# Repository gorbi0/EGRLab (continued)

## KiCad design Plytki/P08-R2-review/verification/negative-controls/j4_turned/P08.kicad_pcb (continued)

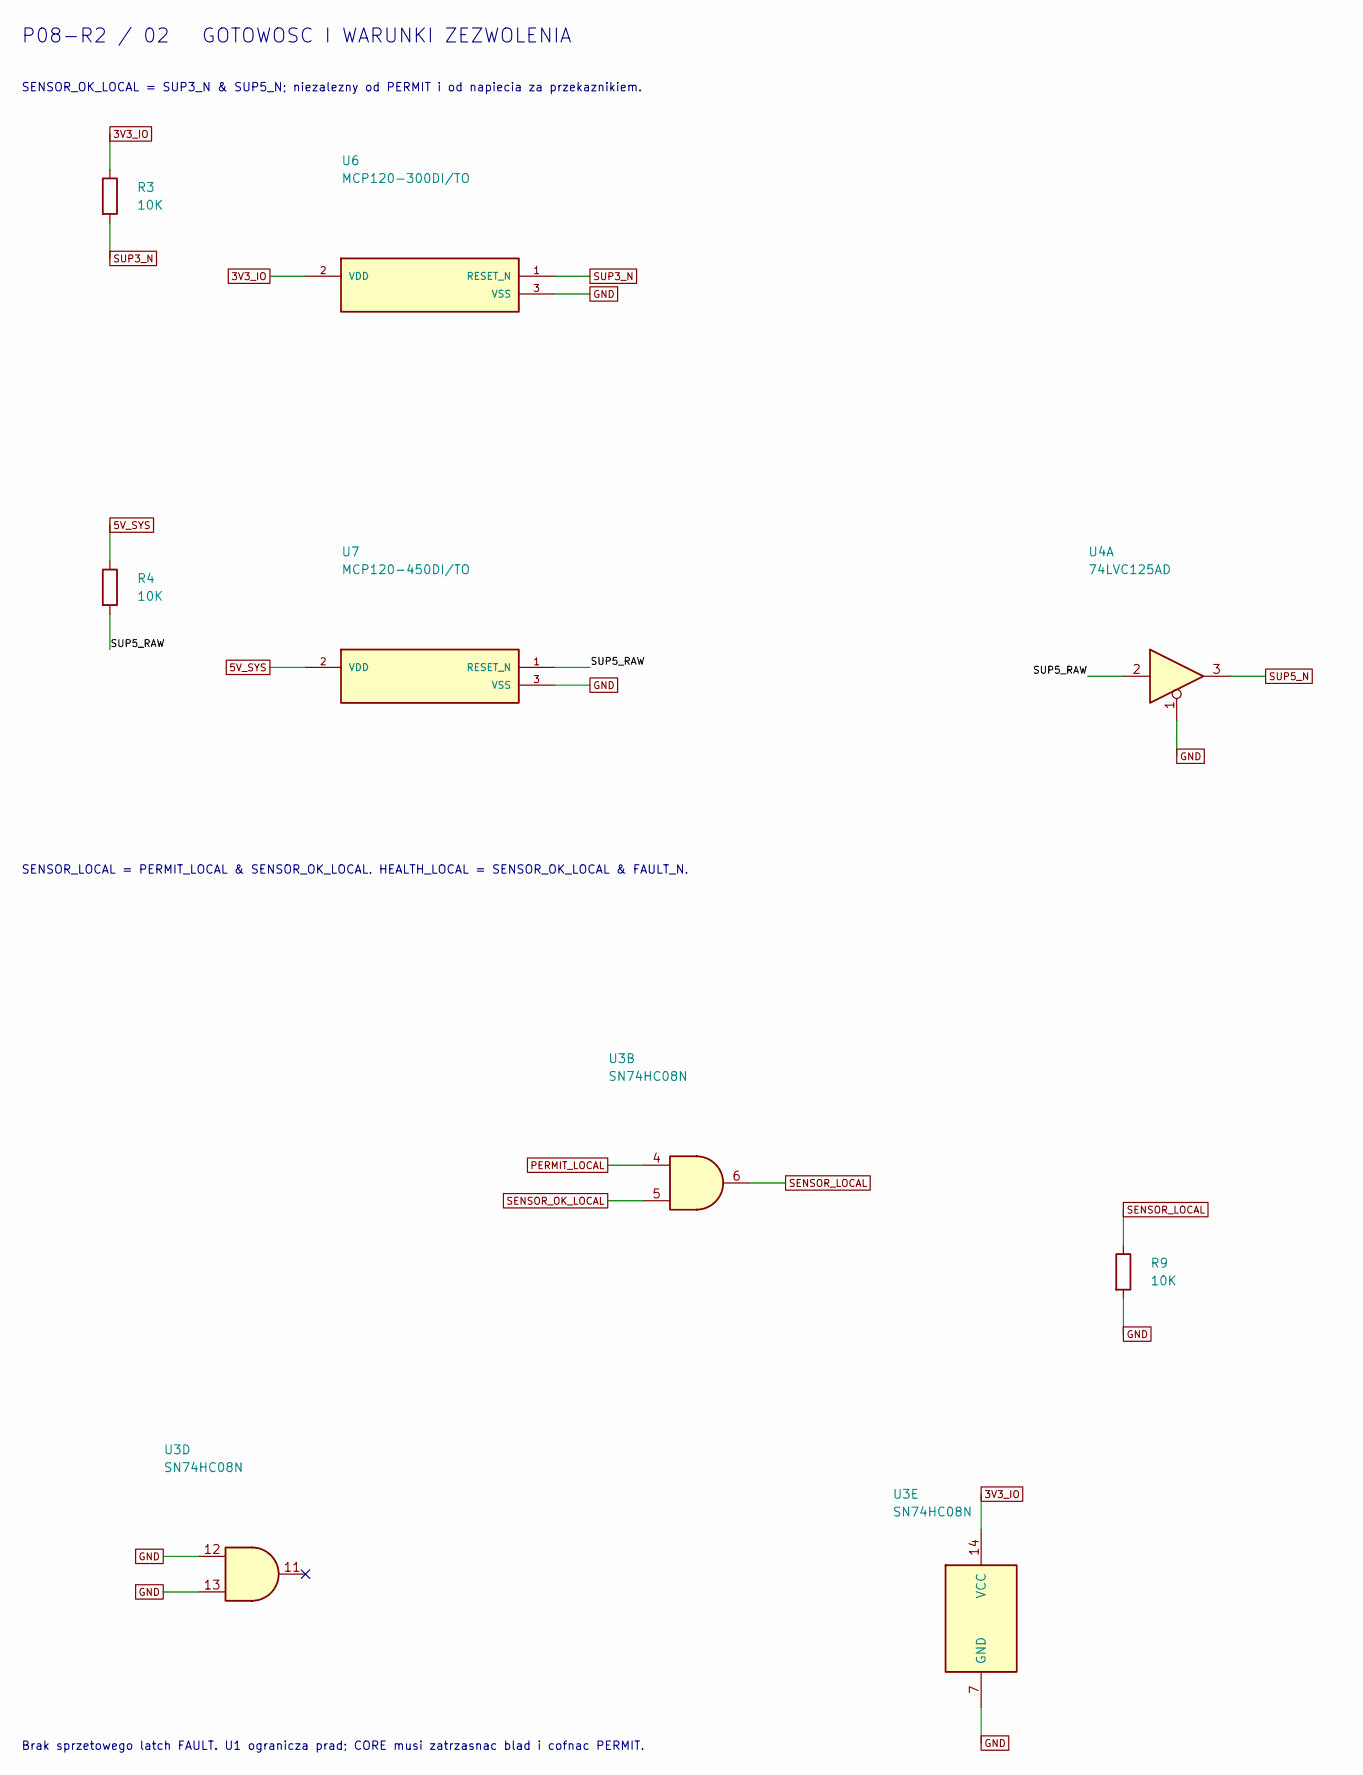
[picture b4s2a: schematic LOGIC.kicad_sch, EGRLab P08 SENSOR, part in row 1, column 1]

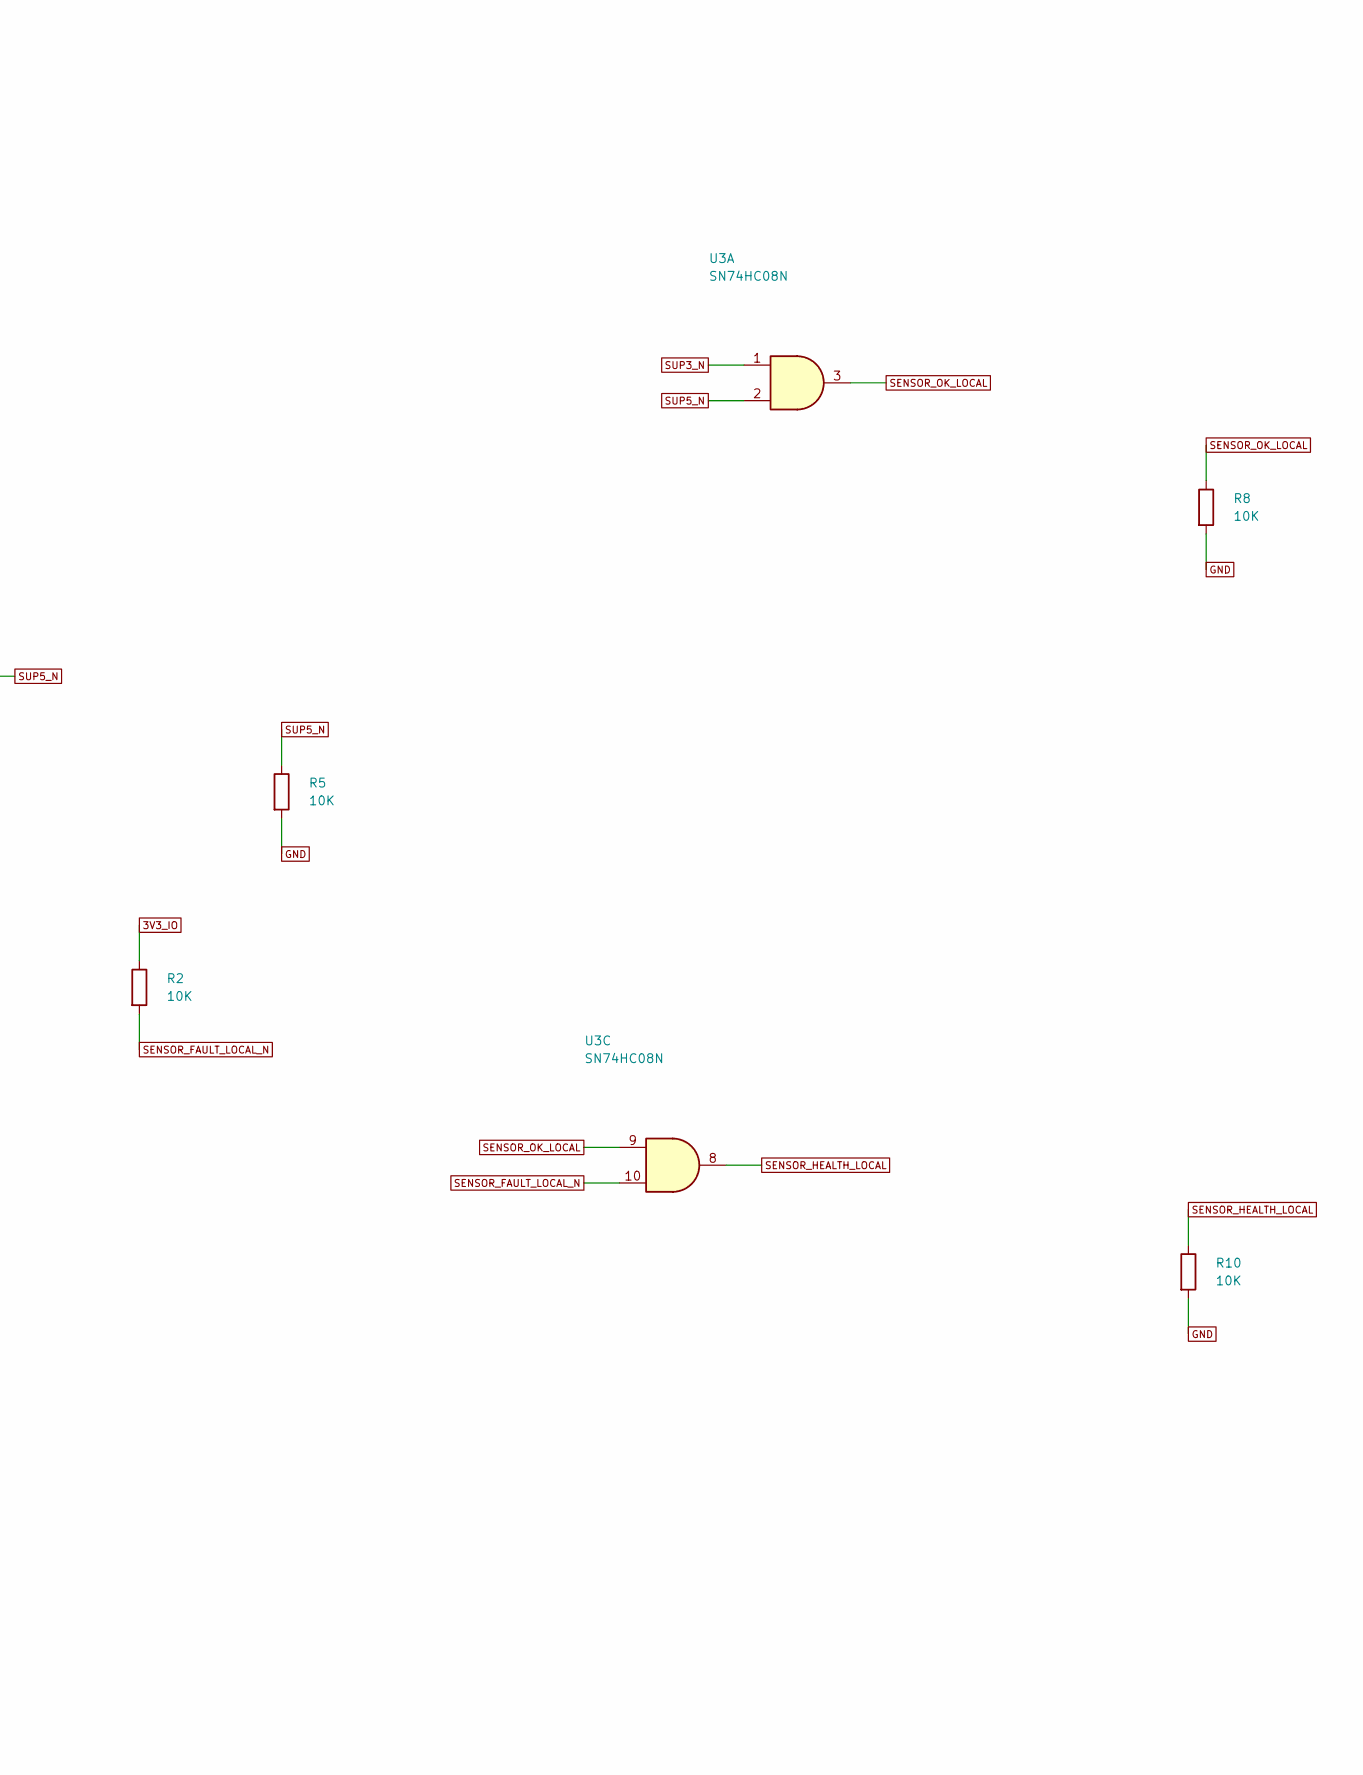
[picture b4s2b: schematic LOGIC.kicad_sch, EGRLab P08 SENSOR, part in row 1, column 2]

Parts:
R2, R3, R4, R5, R8, R9, R10: 10K; R_1206_3216Metric_Pad1.30x1.75mm_HandSolder; MPN SMD 1206 1% 0.25W 10K
U3: SN74HC08N; DIP-14_W7.62mm; MPN SN74HC08N
U4: 74LVC125AD; SOIC-14_3.9x8.7mm_P1.27mm; MPN 74LVC125AD,118 (Nexperia)
U6: MCP120-300DI/TO; TO-92_Inline_Wide; MPN MCP120-300DI/TO
U7: MCP120-450DI/TO; TO-92_Inline_Wide; MPN MCP120-450DI/TO

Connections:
3V3_IO: R2.1, R3.1, U3.14 (VCC), U6.2 (VDD); also elsewhere on the board
5V_SYS: R4.1, U7.2 (VDD); also elsewhere on the board
/LOGIC/SUP5_RAW: R4.2, U4.2, U7.1 (RESET_N)
GND: R5.2, R8.2, R9.2, R10.2, U3.7 (GND), U3.12, U3.13, U4.1, U6.3 (VSS), U7.3 (VSS); also elsewhere on the board
PERMIT_LOCAL: U3.4; also elsewhere on the board
SENSOR_FAULT_LOCAL_N: R2.2, U3.10; also elsewhere on the board
SENSOR_HEALTH_LOCAL: R10.1, U3.8; also elsewhere on the board
SENSOR_LOCAL: R9.1, U3.6; also elsewhere on the board
SENSOR_OK_LOCAL: R8.1, U3.3, U3.5, U3.9; also elsewhere on the board
SUP3_N: R3.2, U3.1, U6.1 (RESET_N); also elsewhere on the board
SUP5_N: R5.1, U3.2, U4.3; also elsewhere on the board

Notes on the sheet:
SENSOR_OK_LOCAL = SUP3_N & SUP5_N; niezalezny od PERMIT i od napiecia za przekaznikiem.
SENSOR_LOCAL = PERMIT_LOCAL & SENSOR_OK_LOCAL. HEALTH_LOCAL = SENSOR_OK_LOCAL & FAULT_N.
Brak sprzetowego latch FAULT. U1 ogranicza prad; CORE musi zatrzasnac blad i cofnac PERMIT.
P08-R2 / 02 GOTOWOSC I WARUNKI ZEZWOLENIA

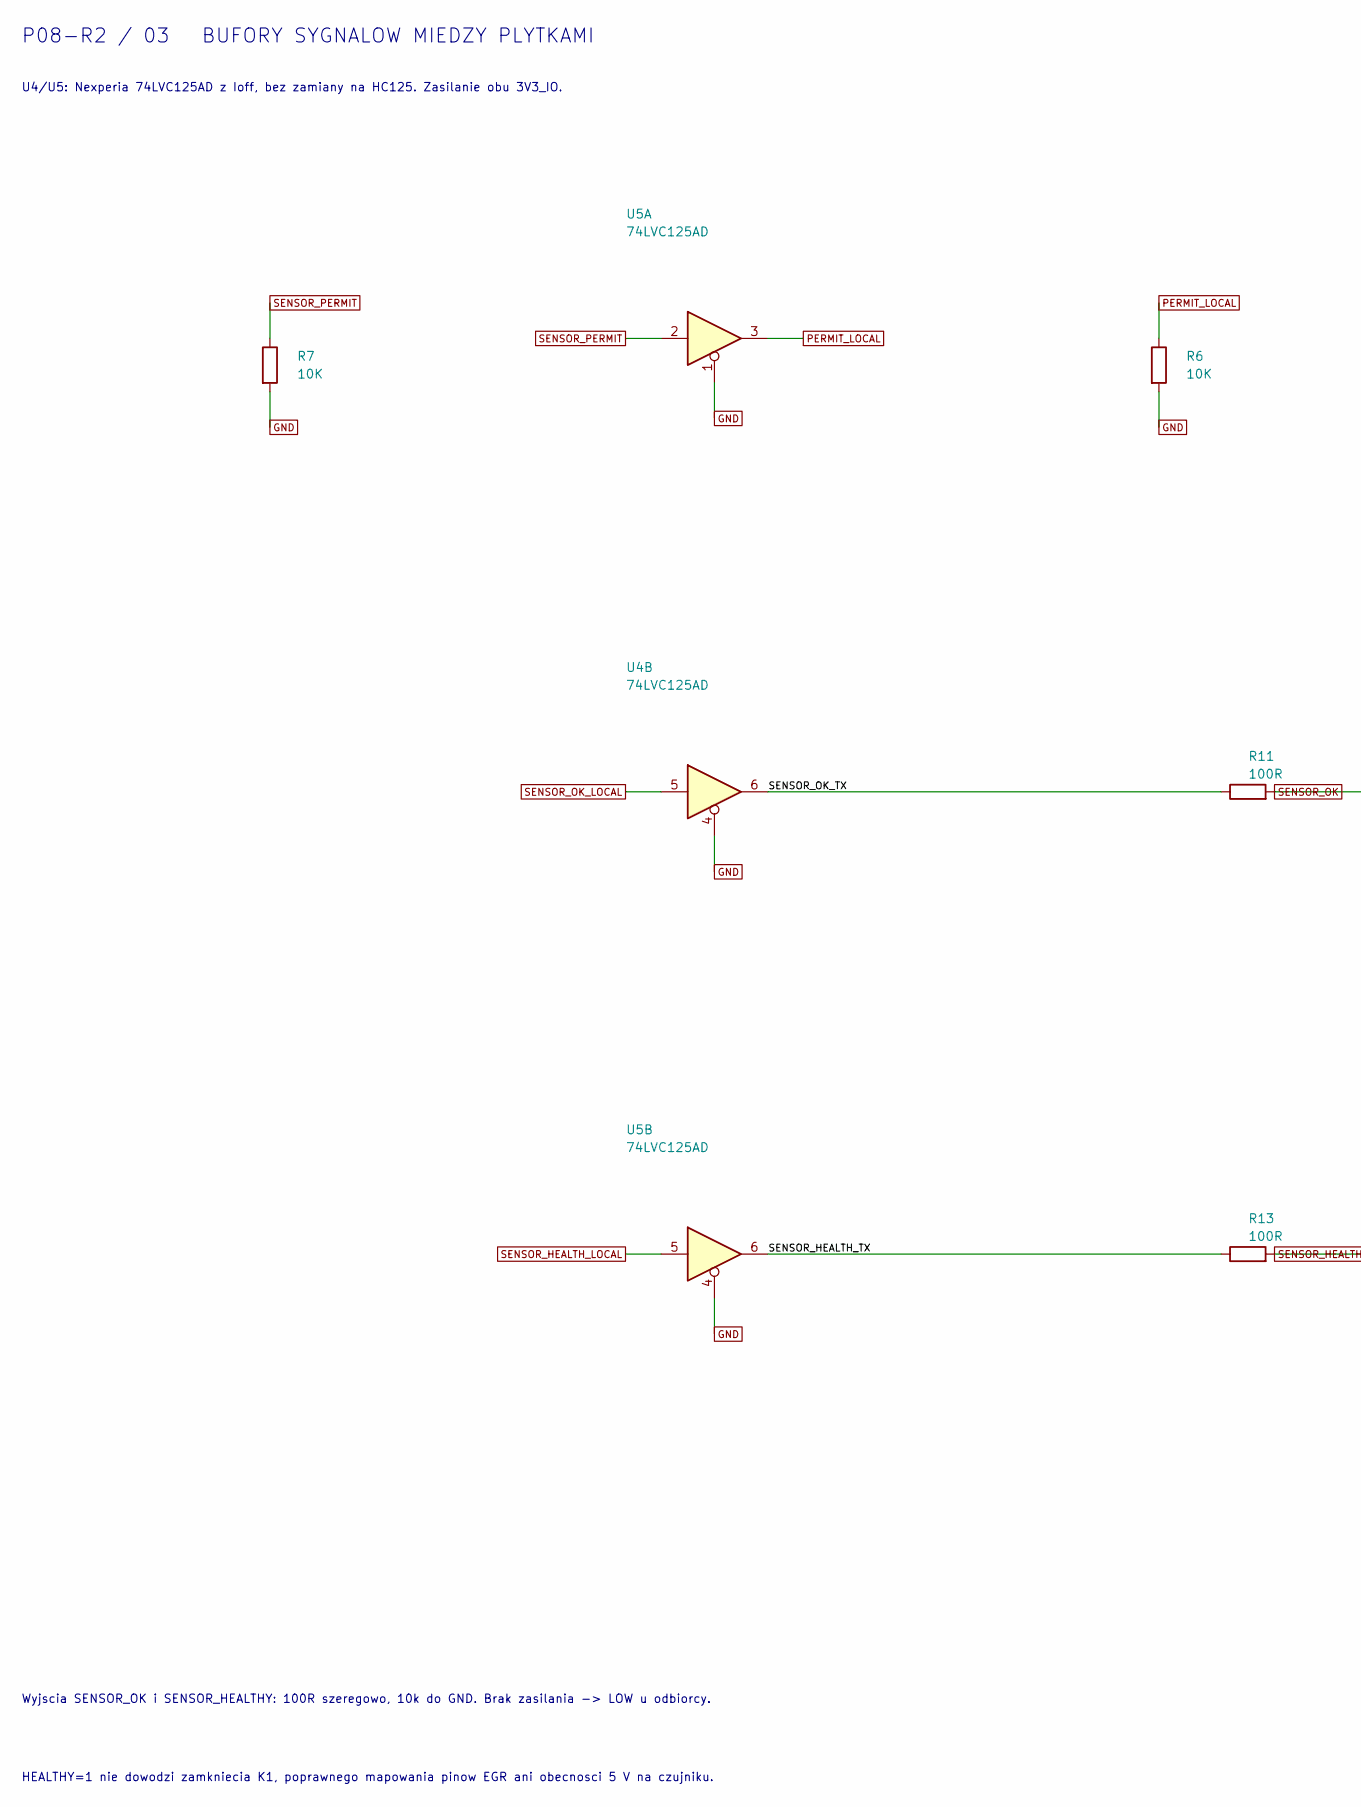
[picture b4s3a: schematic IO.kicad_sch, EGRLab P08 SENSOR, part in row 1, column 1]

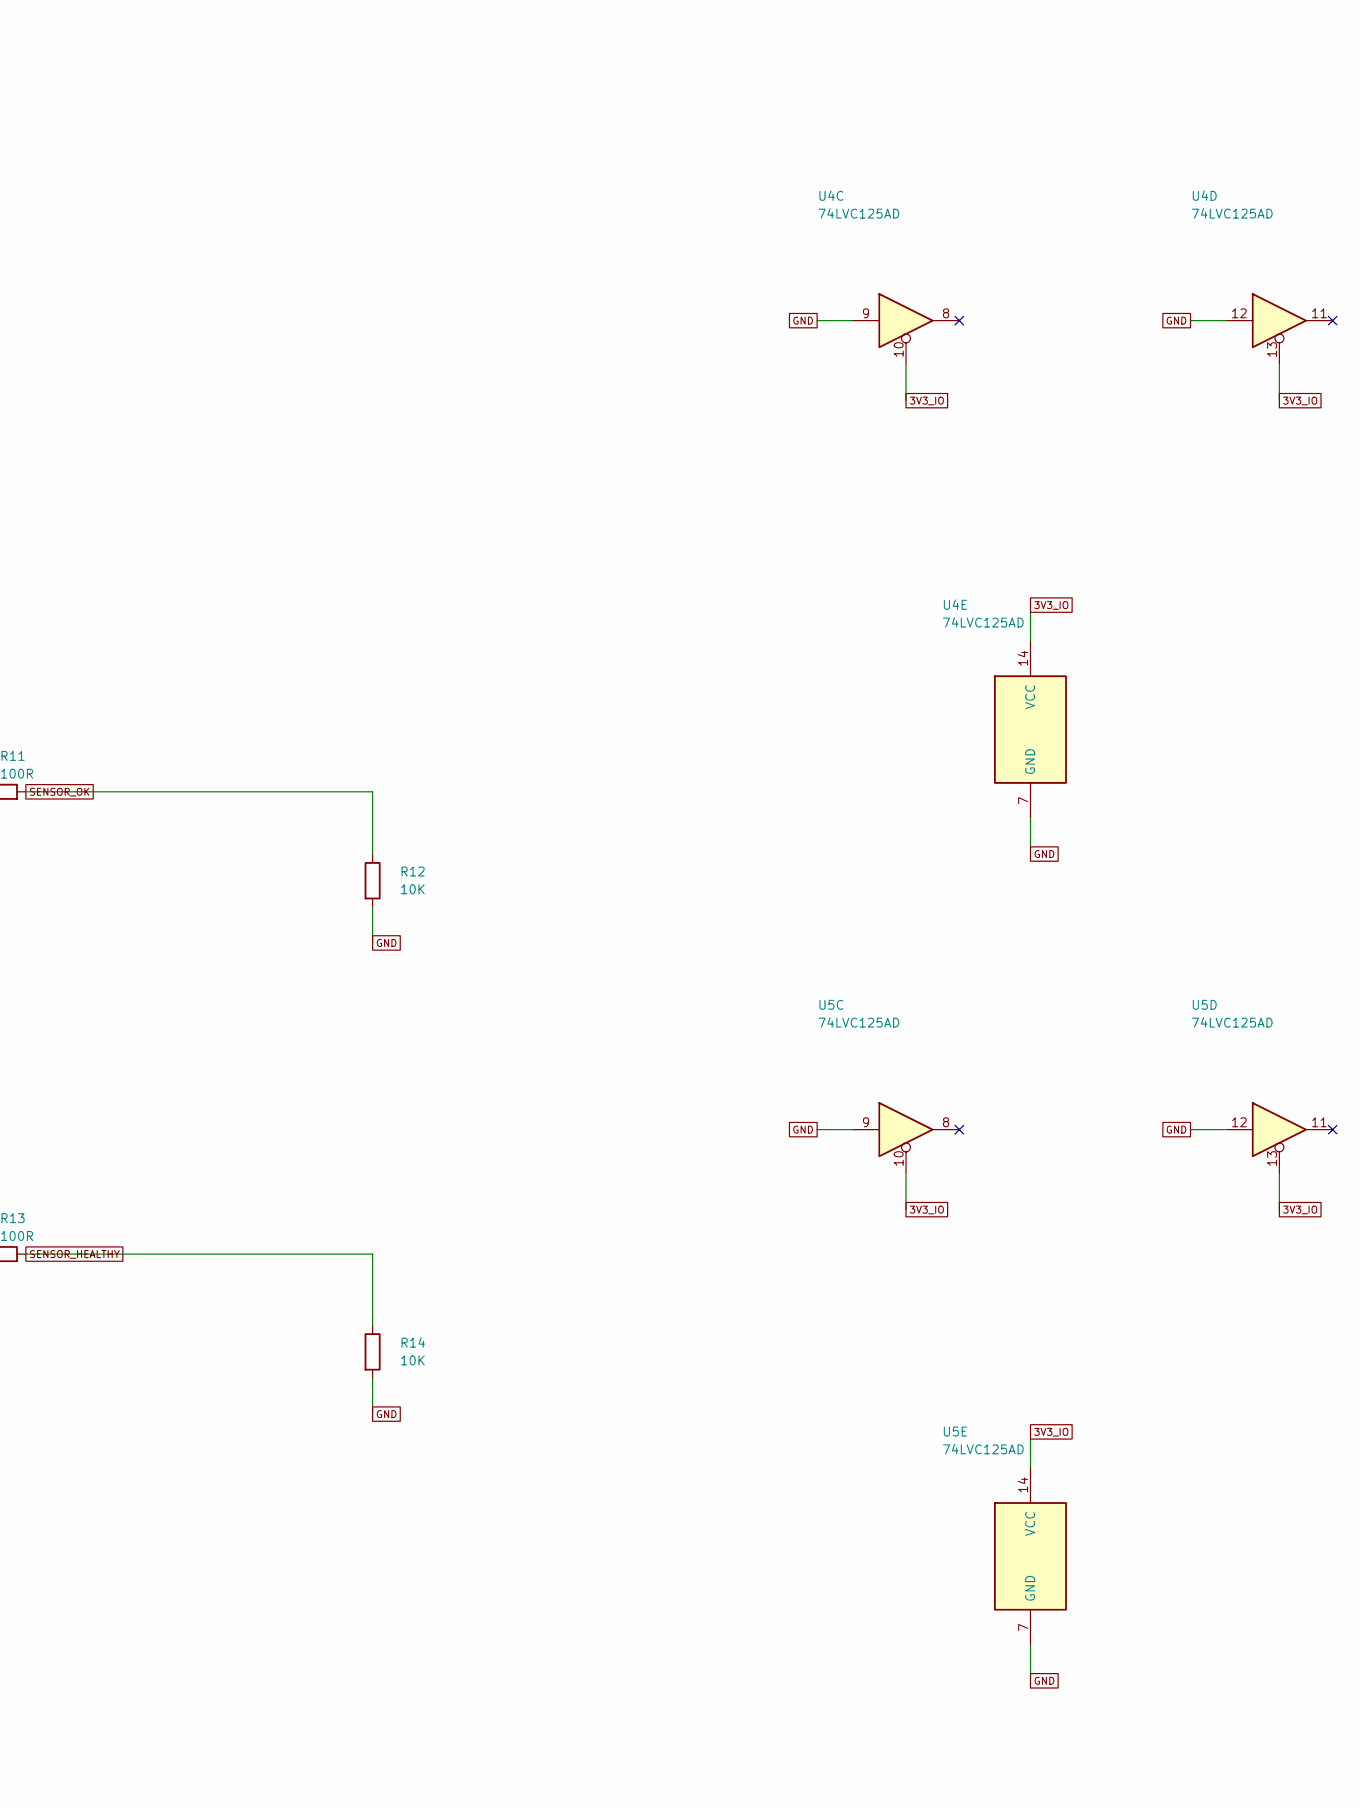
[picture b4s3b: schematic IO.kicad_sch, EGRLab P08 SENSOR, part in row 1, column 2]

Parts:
R6, R7, R12, R14: 10K; R_1206_3216Metric_Pad1.30x1.75mm_HandSolder; MPN SMD 1206 1% 0.25W 10K
R11, R13: 100R; R_1206_3216Metric_Pad1.30x1.75mm_HandSolder; MPN SMD 1206 1% 0.25W 100R
U4, U5: 74LVC125AD; SOIC-14_3.9x8.7mm_P1.27mm; MPN 74LVC125AD,118 (Nexperia)

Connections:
3V3_IO: U4.10, U4.13, U4.14 (VCC), U5.10, U5.13, U5.14 (VCC); also elsewhere on the board
/IO/SENSOR_HEALTH_TX: R13.1, U5.6
/IO/SENSOR_OK_TX: R11.1, U4.6
GND: R6.2, R7.2, R12.2, R14.2, U4.4, U4.7 (GND), U4.9, U4.12, U5.1, U5.4, U5.7 (GND), U5.9, U5.12; also elsewhere on the board
PERMIT_LOCAL: R6.1, U5.3; also elsewhere on the board
SENSOR_HEALTHY: R13.2, R14.1; also elsewhere on the board
SENSOR_HEALTH_LOCAL: U5.5; also elsewhere on the board
SENSOR_OK: R11.2, R12.1; also elsewhere on the board
SENSOR_OK_LOCAL: U4.5; also elsewhere on the board
SENSOR_PERMIT: R7.1, U5.2; also elsewhere on the board

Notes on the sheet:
U4/U5: Nexperia 74LVC125AD z Ioff, bez zamiany na HC125. Zasilanie obu 3V3_IO.
Wyjscia SENSOR_OK i SENSOR_HEALTHY: 100R szeregowo, 10k do GND. Brak zasilania -> LOW u odbiorcy.
HEALTHY=1 nie dowodzi zamkniecia K1, poprawnego mapowania pinow EGR ani obecnosci 5 V na czujniku.
P08-R2 / 03 BUFORY SYGNALOW MIEDZY PLYTKAMI

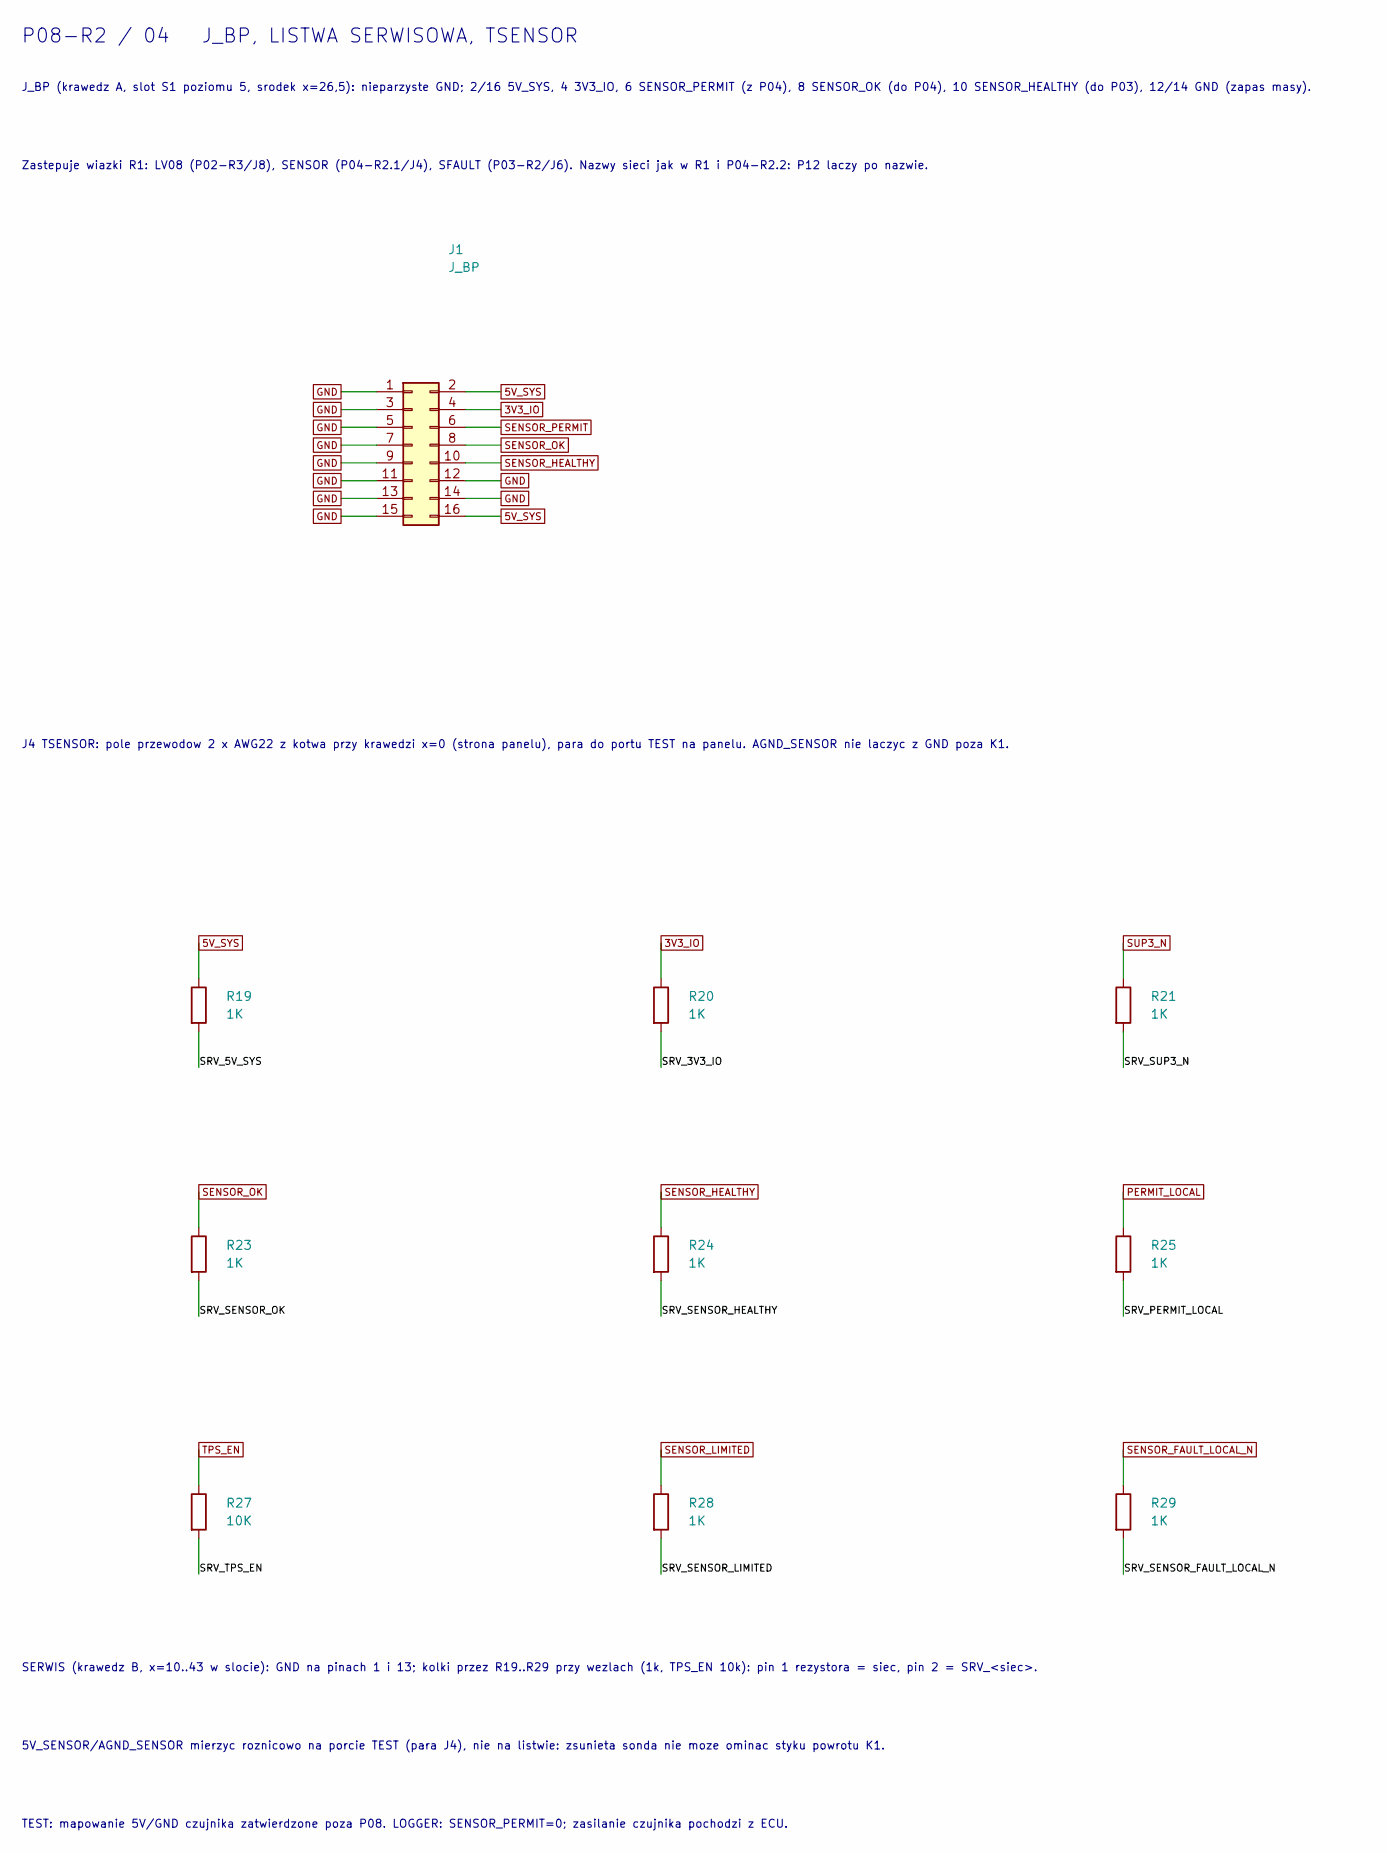
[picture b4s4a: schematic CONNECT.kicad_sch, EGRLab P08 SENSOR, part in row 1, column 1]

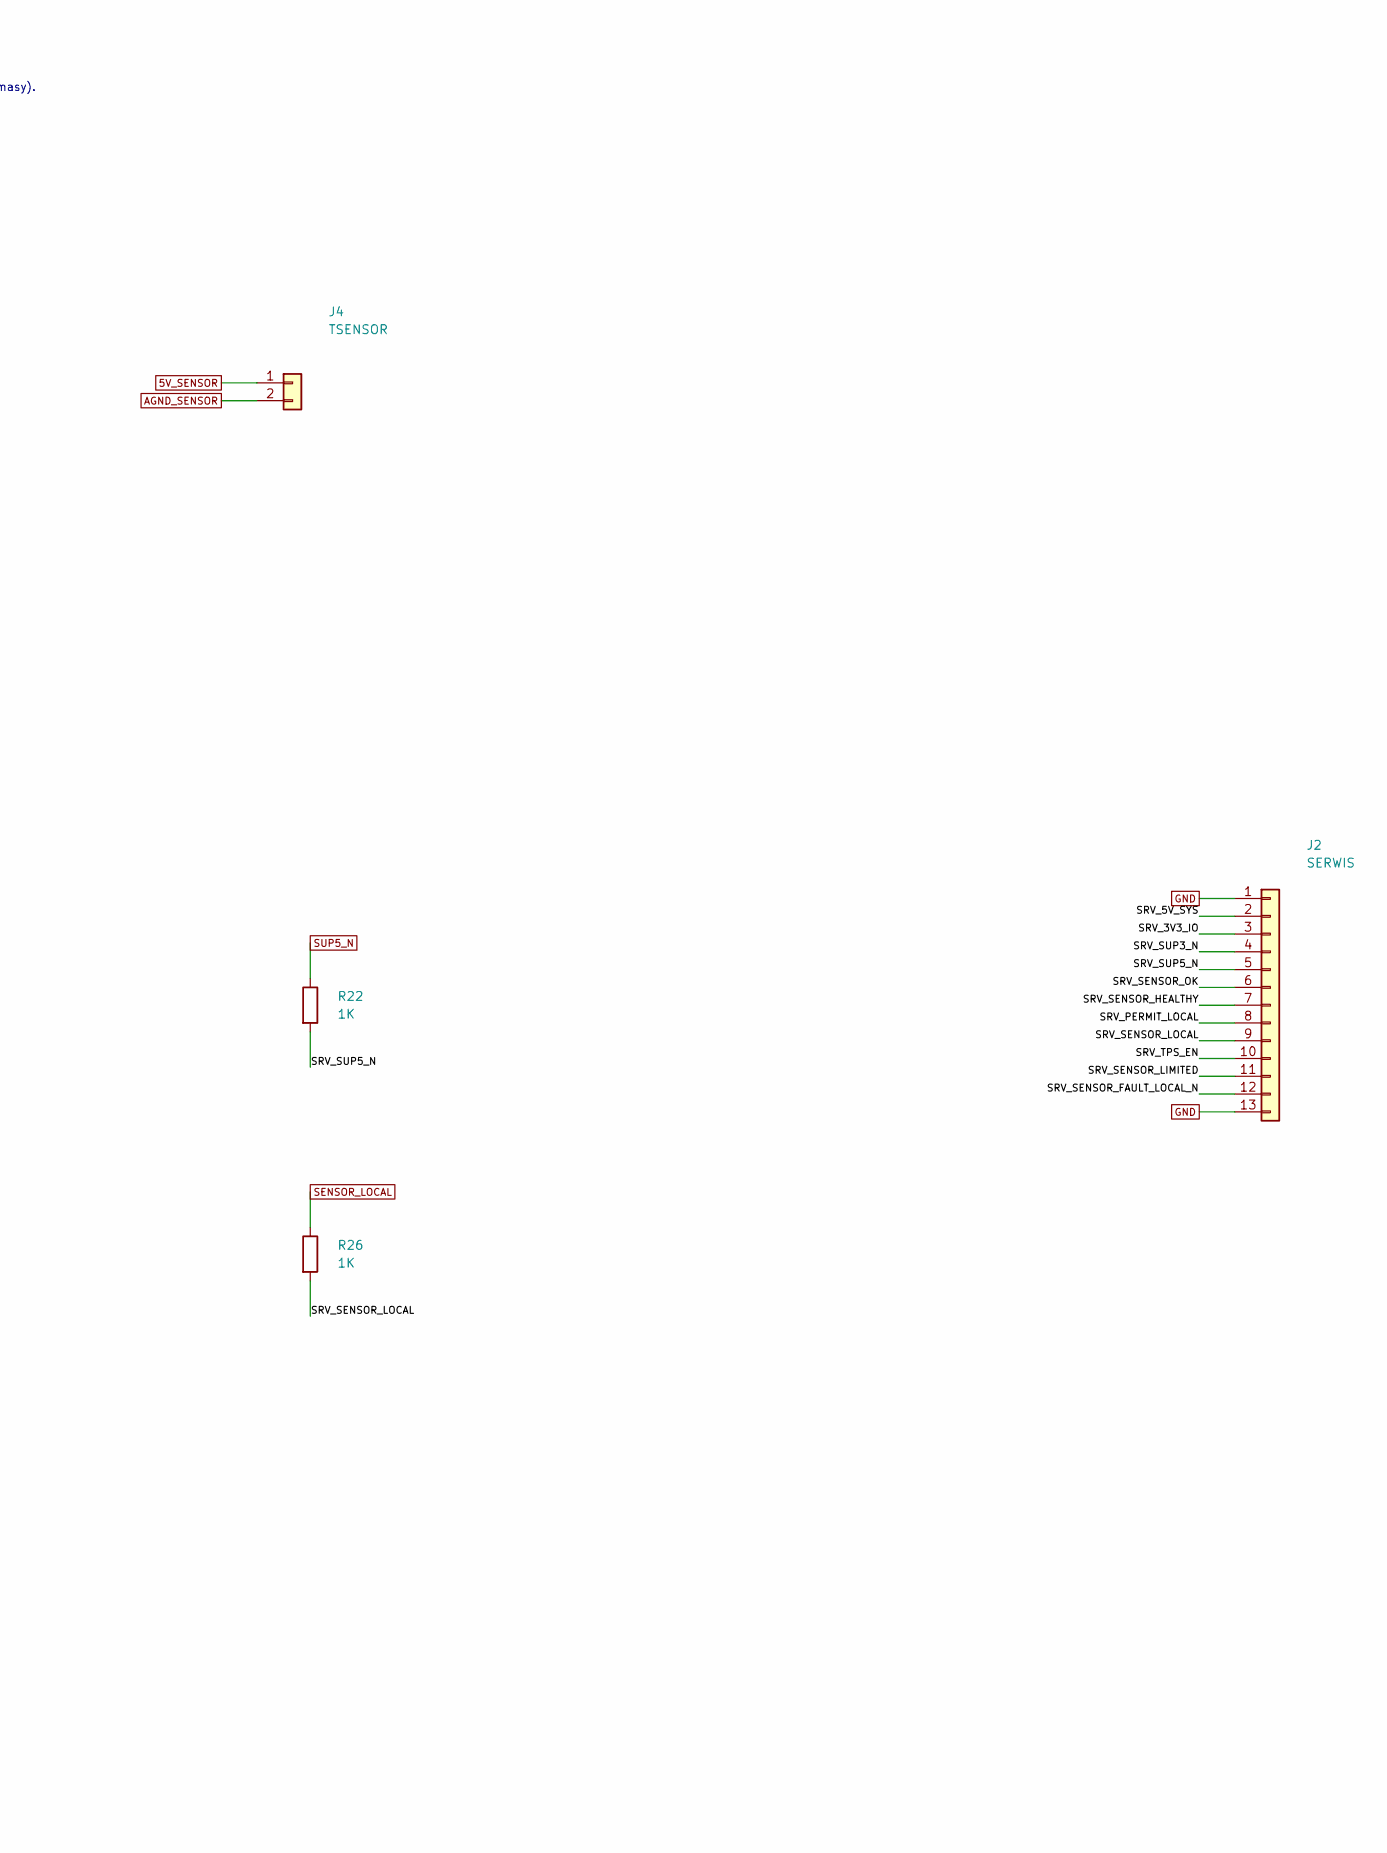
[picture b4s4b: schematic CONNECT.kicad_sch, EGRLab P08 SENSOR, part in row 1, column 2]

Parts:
J1: J_BP; IDC-Header_2x08_P2.54mm_Horizontal; MPN IDC header 2x8 2.54mm angled shrouded, 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
J2: SERWIS; PinHeader_1x13_P2.54mm_Horizontal; MPN Goldpin 1x13 2.54mm angled (buy angled 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
J4: TSENSOR; PTH_TSENSOR_2; MPN 2 x AWG22 soldered, tie anchor 12 mm
R19, R20, R21, R22, R23, R24, R25, R26, R28, R29: 1K; R_1206_3216Metric_Pad1.30x1.75mm_HandSolder; MPN SMD 1206 1% 0.25W 1K
R27: 10K; R_1206_3216Metric_Pad1.30x1.75mm_HandSolder; MPN SMD 1206 1% 0.25W 10K

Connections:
3V3_IO: J1.4, R20.1; also elsewhere on the board
5V_SENSOR: J4.1; also elsewhere on the board
5V_SYS: J1.2, J1.16, R19.1; also elsewhere on the board
/CONNECT/SRV_3V3_IO: J2.3, R20.2
/CONNECT/SRV_5V_SYS: J2.2, R19.2
/CONNECT/SRV_PERMIT_LOCAL: J2.8, R25.2
/CONNECT/SRV_SENSOR_FAULT_LOCAL_N: J2.12, R29.2
/CONNECT/SRV_SENSOR_HEALTHY: J2.7, R24.2
/CONNECT/SRV_SENSOR_LIMITED: J2.11, R28.2
/CONNECT/SRV_SENSOR_LOCAL: J2.9, R26.2
/CONNECT/SRV_SENSOR_OK: J2.6, R23.2
/CONNECT/SRV_SUP3_N: J2.4, R21.2
/CONNECT/SRV_SUP5_N: J2.5, R22.2
/CONNECT/SRV_TPS_EN: J2.10, R27.2
AGND_SENSOR: J4.2; also elsewhere on the board
GND: J1.1, J1.3, J1.5, J1.7, J1.9, J1.11, J1.12, J1.13, J1.14, J1.15, J2.1, J2.13; also elsewhere on the board
PERMIT_LOCAL: R25.1; also elsewhere on the board
SENSOR_FAULT_LOCAL_N: R29.1; also elsewhere on the board
SENSOR_HEALTHY: J1.10, R24.1; also elsewhere on the board
SENSOR_LIMITED: R28.1; also elsewhere on the board
SENSOR_LOCAL: R26.1; also elsewhere on the board
SENSOR_OK: J1.8, R23.1; also elsewhere on the board
SENSOR_PERMIT: J1.6; also elsewhere on the board
SUP3_N: R21.1; also elsewhere on the board
SUP5_N: R22.1; also elsewhere on the board
TPS_EN: R27.1; also elsewhere on the board

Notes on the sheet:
J_BP (krawedz A, slot S1 poziomu 5, srodek x=26,5): nieparzyste GND; 2/16 5V_SYS, 4 3V3_IO, 6 SENSOR_PERMIT (z P04), 8 SENSOR_OK (do P04), 10 SENSOR_HEALTHY (do P03), 12/14 GND (zapas masy).
Zastepuje wiazki R1: LV08 (P02-R3/J8), SENSOR (P04-R2.1/J4), SFAULT (P03-R2/J6). Nazwy sieci jak w R1 i P04-R2.2: P12 laczy po nazwie.
J4 TSENSOR: pole przewodow 2 x AWG22 z kotwa przy krawedzi x=0 (strona panelu), para do portu TEST na panelu. AGND_SENSOR nie laczyc z GND poza K1.
SERWIS (krawedz B, x=10..43 w slocie): GND na pinach 1 i 13; kolki przez R19..R29 przy wezlach (1k, TPS_EN 10k): pin 1 rezystora = siec, pin 2 = SRV_<siec>.
5V_SENSOR/AGND_SENSOR mierzyc roznicowo na porcie TEST (para J4), nie na listwie: zsunieta sonda nie moze ominac styku powrotu K1.
TEST: mapowanie 5V/GND czujnika zatwierdzone poza P08. LOGGER: SENSOR_PERMIT=0; zasilanie czujnika pochodzi z ECU.
P08-R2 / 04 J_BP, LISTWA SERWISOWA, TSENSOR

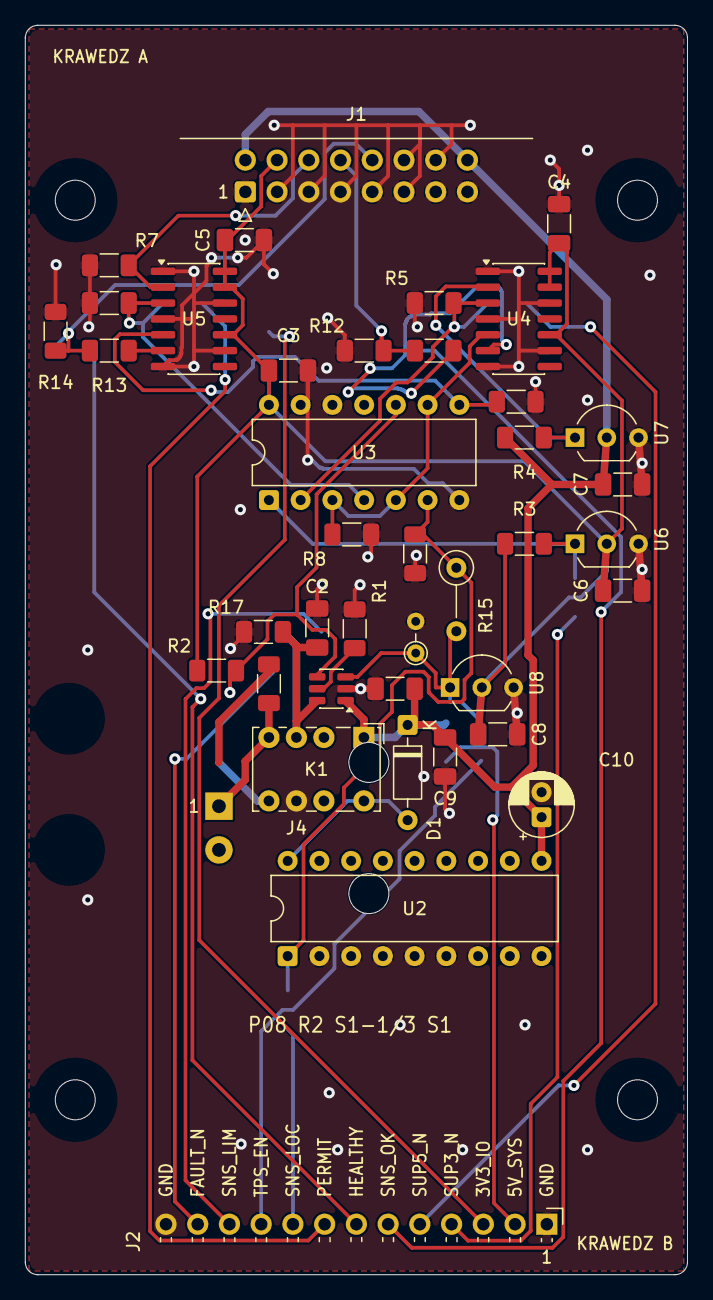
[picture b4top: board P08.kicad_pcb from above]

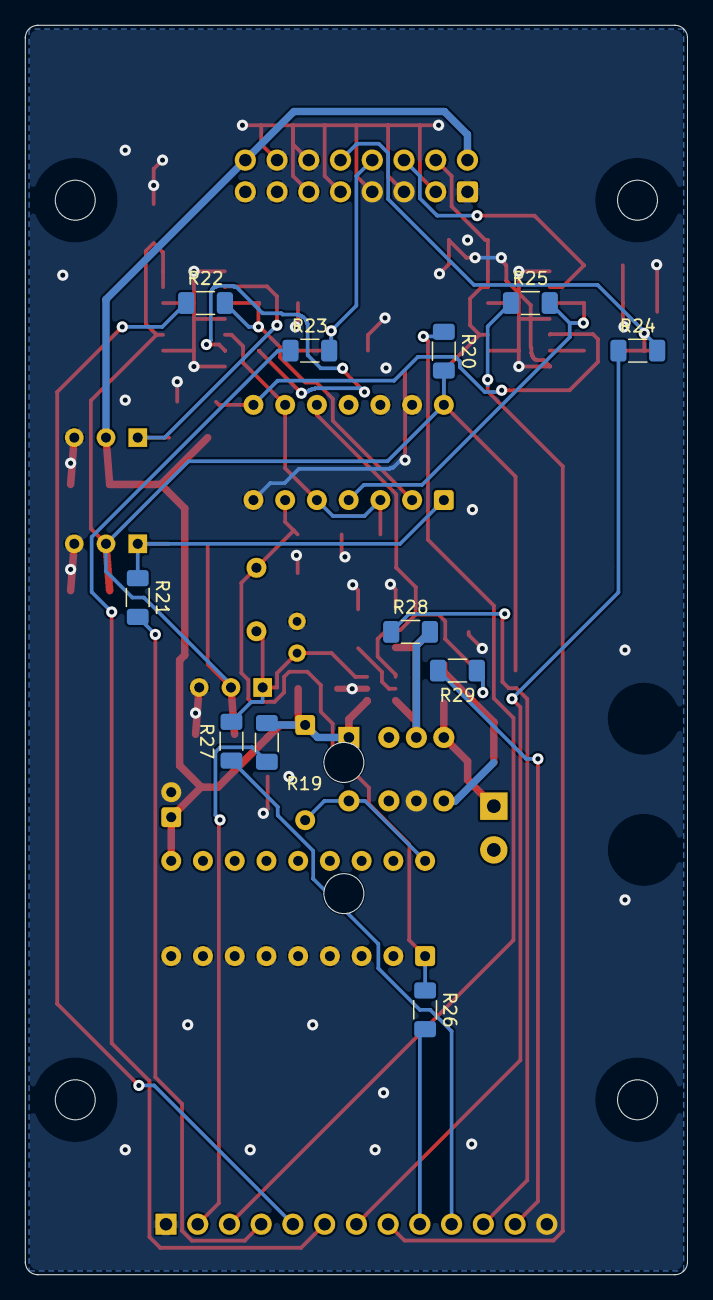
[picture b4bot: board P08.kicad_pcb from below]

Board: 2 copper layers, 53.0 x 100.0 mm, 56 parts (11 on the bottom side), 33 nets.

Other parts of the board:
H1, H2, H3, H4: M3 NPTH
